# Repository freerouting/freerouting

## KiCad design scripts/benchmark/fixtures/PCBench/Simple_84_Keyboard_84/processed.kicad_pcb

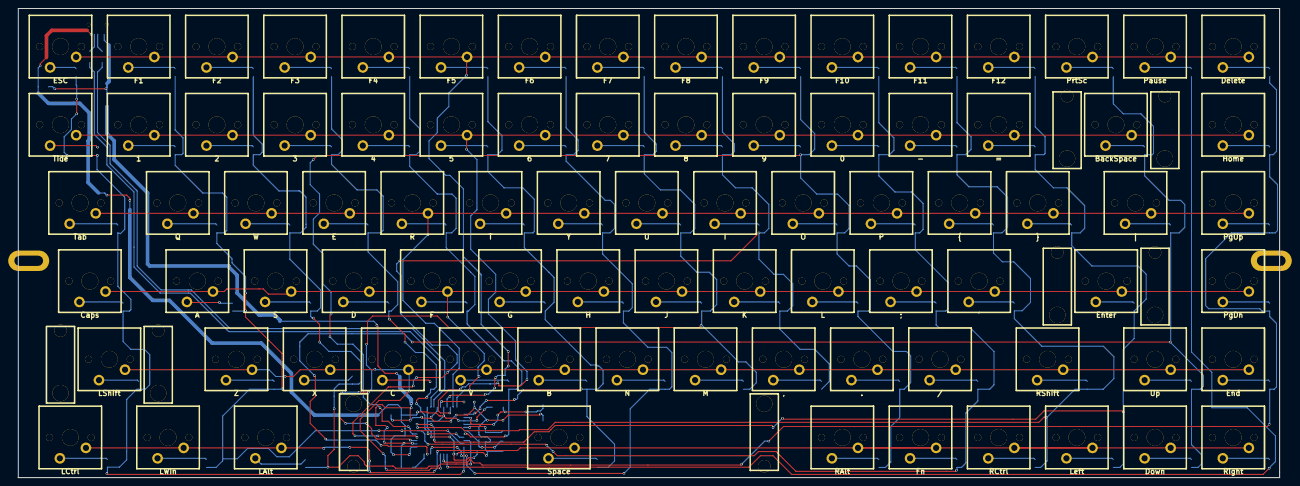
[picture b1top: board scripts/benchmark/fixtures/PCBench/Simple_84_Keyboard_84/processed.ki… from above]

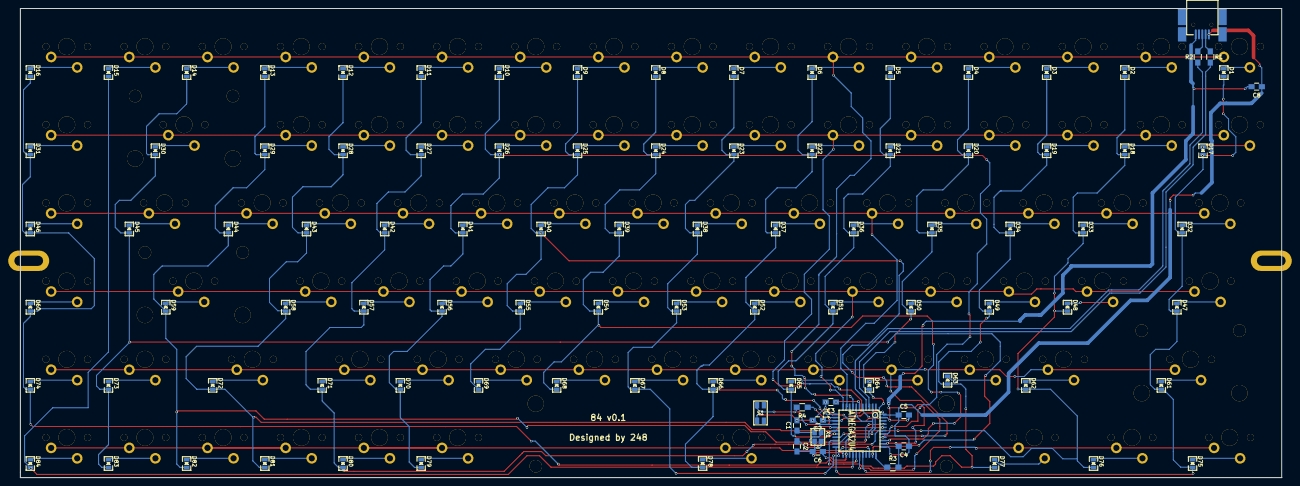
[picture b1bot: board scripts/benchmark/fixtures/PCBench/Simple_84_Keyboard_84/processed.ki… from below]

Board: 2 copper layers, 307.3 x 114.3 mm, 194 parts (100 on the bottom side), 117 nets.

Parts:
C1, C2: 22pF; C_0805_HandSoldering
C3, C8: 1uF; C_0805_HandSoldering
C4, C5, C6, C7: 100nF; C_0805_HandSoldering
D1, D2, D3, D4, D5, D6, D7, D8, D9, D10, D11, D12, D13, D14, D15, D16, D17, D18, D19, D20, D21, D22, D23, D24, D25, D26, D27, D28, D29, D30, D31, D32, D33, D34, D35, D36, D37, D38, D39, D40, D41, D42, D43, D44, D45, D46, D47, D48, D49, D50, D51, D52, D53, D54, D55, D56, D57, D58, D59, D60, D61, D62, D63, D64, D65, D66, D67, D68, D69, D70, D71, D72, D73, D74, D75, D76, D77, D78, D79, D80, D81, D82, D83, D84: DIODE; SM0805D
IC1: ATMEGA32U4; TQFP44
J1: USBMINI_B05; 67503
MXLED: VAL**; PKRHSL
MXLED_2: VAL**; PKRHSL
MXST: VAL**; MXST
MXST_2, MXST_3, MXST_4, MXST_5, MXST_6, MXST_7, MXST_8: VAL**; MXST
R1, R2: 22R; R_0805_HandSoldering
R3, R4: 10K; R_0805_HandSoldering
S1: DTSM-6; TACT_4x3
S2: ESC; MX1A-simple
S3: F1; MX1A-simple
S4: F2; MX1A-simple
S5: F3; MX1A-simple
S6: F4; MX1A-simple
S7: F5; MX1A-simple
S8: F6; MX1A-simple
S9: F7; MX1A-simple
S10: F8; MX1A-simple
S11: F9; MX1A-simple
S12: F10; MX1A-simple
S13: F11; MX1A-simple
S14: F12; MX1A-simple
S15: PrtSc; MX1A-simple
S16: Pause; MX1A-simple
S17: Delete; MX1A-simple
S18: Tide; MX1A-simple
S19: 1; MX1A-simple
S20: 2; MX1A-simple
S21: 3; MX1A-simple
S22: 4; MX1A-simple
S23: 5; MX1A-simple
S24: 6; MX1A-simple
S25: 7; MX1A-simple
S26: 8; MX1A-simple
S27: 9; MX1A-simple
S28: 0; MX1A-simple
S29: -; MX1A-simple
S30: =; MX1A-simple
S31: BackSpace; MX1A-simple
S32: Home; MX1A-simple
S33: Tab; MX1A-simple
S34: Q; MX1A-simple
S35: W; MX1A-simple
S36: E; MX1A-simple
S37: R; MX1A-simple
S38: T; MX1A-simple
S39: Y; MX1A-simple
S40: U; MX1A-simple
S41: I; MX1A-simple
S42: O; MX1A-simple
S43: P; MX1A-simple
S44: {; MX1A-simple
S45: }; MX1A-simple
S46: |; MX1A-simple
S47: PgUp; MX1A-simple
S48: Caps; MX1A-simple
S49: A; MX1A-simple
S50: S; MX1A-simple
S51: D; MX1A-simple
S52: F; MX1A-simple
S53: G; MX1A-simple
S54: H; MX1A-simple
S55: J; MX1A-simple
S56: K; MX1A-simple
S57: L; MX1A-simple
S58: ;; MX1A-simple
S59: '; MX1A-simple
S60: Enter; MX1A-simple
S61: PgDn; MX1A-simple
S62: LShift; MX1A-simple
S63: Z; MX1A-simple
S64: X; MX1A-simple
S65: C; MX1A-simple
S66: V; MX1A-simple
S67: B; MX1A-simple
S68: N; MX1A-simple
S69: M; MX1A-simple
S70: ,; MX1A-simple
S71: .; MX1A-simple
S72: /; MX1A-simple
S73: RShift; MX1A-simple
S74: Up; MX1A-simple
S75: End; MX1A-simple
S76: LCtrl; MX1A-simple
S77: LWin; MX1A-simple
S78: LAlt; MX1A-simple
S79: Space; MX1A-simple
S80: RAlt; MX1A-simple
S81: Fn; MX1A-simple
S82: RCtrl; MX1A-simple
S83: Left; MX1A-simple
S84: Down; MX1A-simple
S85: Right; MX1A-simple
X1: ASX4; ASX3F

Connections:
/switch_matrix/Col1: D1.1, D17.1, D32.1, D47.1, D61.1, D75.1, IC1.22
/switch_matrix/Col2: D2.1, D18.1, D33.1, D48.1, D62.1, D76.1, IC1.21
/switch_matrix/Col3: D3.1, D19.1, D34.1, D49.1, D63.1, D77.1, IC1.20
/switch_matrix/Col4: D4.1, D20.1, D35.1, D50.1, D64.1, IC1.19
/switch_matrix/Col5: D5.1, D21.1, D36.1, D51.1, D65.1, IC1.18
/switch_matrix/Col6: D6.1, D22.1, D37.1, D52.1, D66.1, D78.1, IC1.12
/switch_matrix/Col7: D7.1, D23.1, D38.1, D53.1, D67.1, IC1.31
/switch_matrix/Col8: D8.1, D24.1, D39.1, D54.1, D68.1, IC1.36
/switch_matrix/Col9: D9.1, D25.1, D40.1, D55.1, D69.1, IC1.37
/switch_matrix/Col10: D10.1, D26.1, D41.1, D56.1, D70.1, D79.1, IC1.38
/switch_matrix/Col11: D11.1, D27.1, D42.1, D57.1, D71.1, D80.1, IC1.39
/switch_matrix/Col12: D12.1, D28.1, D43.1, D58.1, D72.1, D81.1, IC1.40
/switch_matrix/Col13: D13.1, D29.1, D44.1, D59.1, D82.1, IC1.41
/switch_matrix/Col14: D14.1, D30.1, D45.1, D73.1, D83.1, IC1.32
/switch_matrix/Col15: D15.1, D84.1, IC1.26
/switch_matrix/Col16: D16.1, D31.1, D46.1, D60.1, D74.1, IC1.27
/switch_matrix/Row1: IC1.8, S2.1, S3.1, S4.1, S5.1, S6.1, S7.1, S8.1, S9.1, S10.1, S11.1, S12.1, S13.1, S14.1, S15.1, S16.1, S17.1
/switch_matrix/Row2: IC1.9, S18.1, S19.1, S20.1, S21.1, S22.1, S23.1, S24.1, S25.1, S26.1, S27.1, S28.1, S29.1, S30.1, S31.1, S32.1
/switch_matrix/Row3: IC1.10, S33.1, S34.1, S35.1, S36.1, S37.1, S38.1, S39.1, S40.1, S41.1, S42.1, S43.1, S44.1, S45.1, S46.1, S47.1
/switch_matrix/Row4: IC1.11, S48.1, S49.1, S50.1, S51.1, S52.1, S53.1, S54.1, S55.1, S56.1, S57.1, S58.1, S59.1, S60.1, S61.1
/switch_matrix/Row5: IC1.28, S62.1, S63.1, S64.1, S65.1, S66.1, S67.1, S68.1, S69.1, S70.1, S71.1, S72.1, S73.1, S74.1, S75.1
/switch_matrix/Row6: IC1.29, S76.1, S77.1, S78.1, S79.1, S80.1, S81.1, S82.1, S83.1, S84.1, S85.1
GND: C1.2, C2.2, C3.2, C4.2, C5.2, C6.2, C7.2, C8.2, IC1.5, IC1.15, IC1.23, IC1.35, IC1.43, J1.5, R3.2, S1.1, X1.2, X1.4
unnamed: C1.1, IC1.16, X1.1
unnamed: C2.1, IC1.17, X1.3
unnamed: C3.1, IC1.6
unnamed: D1.2, S2.2
unnamed: D2.2, S3.2
unnamed: D3.2, S4.2
unnamed: D4.2, S5.2
unnamed: D5.2, S6.2
unnamed: D6.2, S7.2
unnamed: D7.2, S8.2
unnamed: D8.2, S9.2
unnamed: D9.2, S10.2
unnamed: D10.2, S11.2
unnamed: D11.2, S12.2
unnamed: D12.2, S13.2
unnamed: D13.2, S14.2
unnamed: D14.2, S15.2
unnamed: D15.2, S16.2
unnamed: D16.2, S17.2
unnamed: D17.2, S18.2
unnamed: D18.2, S19.2
unnamed: D19.2, S20.2
unnamed: D20.2, S21.2
unnamed: D21.2, S22.2
unnamed: D22.2, S23.2
unnamed: D23.2, S24.2
unnamed: D24.2, S25.2
unnamed: D25.2, S26.2
unnamed: D26.2, S27.2
unnamed: D27.2, S28.2
unnamed: D28.2, S29.2
unnamed: D29.2, S30.2
unnamed: D30.2, S31.2
unnamed: D31.2, S32.2
unnamed: D32.2, S33.2
unnamed: D33.2, S34.2
unnamed: D34.2, S35.2
unnamed: D35.2, S36.2
unnamed: D36.2, S37.2
unnamed: D37.2, S38.2
unnamed: D38.2, S39.2
unnamed: D39.2, S40.2
unnamed: D40.2, S41.2
unnamed: D41.2, S42.2
unnamed: D42.2, S43.2
unnamed: D43.2, S44.2
unnamed: D44.2, S45.2
unnamed: D45.2, S46.2
unnamed: D46.2, S47.2
unnamed: D47.2, S48.2
unnamed: D48.2, S49.2
unnamed: D49.2, S50.2
unnamed: D50.2, S51.2
unnamed: D51.2, S52.2
unnamed: D52.2, S53.2
unnamed: D53.2, S54.2
unnamed: D54.2, S55.2
unnamed: D55.2, S56.2
unnamed: D56.2, S57.2
unnamed: D57.2, S58.2
unnamed: D58.2, S59.2
unnamed: D59.2, S60.2
unnamed: D60.2, S61.2
unnamed: D61.2, S62.2
unnamed: D62.2, S63.2
unnamed: D63.2, S64.2
unnamed: D64.2, S65.2
unnamed: D65.2, S66.2
unnamed: D66.2, S67.2
unnamed: D67.2, S68.2
unnamed: D68.2, S69.2
unnamed: D69.2, S70.2
unnamed: D70.2, S71.2
unnamed: D71.2, S72.2
unnamed: D72.2, S73.2
unnamed: D73.2, S74.2
unnamed: D74.2, S75.2
unnamed: D75.2, S76.2
unnamed: D76.2, S77.2
unnamed: D77.2, S78.2
unnamed: D78.2, S79.2
unnamed: D79.2, S80.2
unnamed: D80.2, S81.2
unnamed: D81.2, S82.2
unnamed: D82.2, S83.2
unnamed: D83.2, S84.2
unnamed: D84.2, S85.2
unnamed: IC1.3, R1.2
unnamed: IC1.4, R2.1
unnamed: IC1.13, R4.2, S1.3
unnamed: IC1.33, R3.1
unnamed: J1.2, R1.1
unnamed: J1.3, R2.2
VCC: C4.1, C5.1, C6.1, C7.1, C8.1, IC1.2, IC1.7, IC1.14, IC1.24, IC1.34, IC1.44, J1.1, R4.1

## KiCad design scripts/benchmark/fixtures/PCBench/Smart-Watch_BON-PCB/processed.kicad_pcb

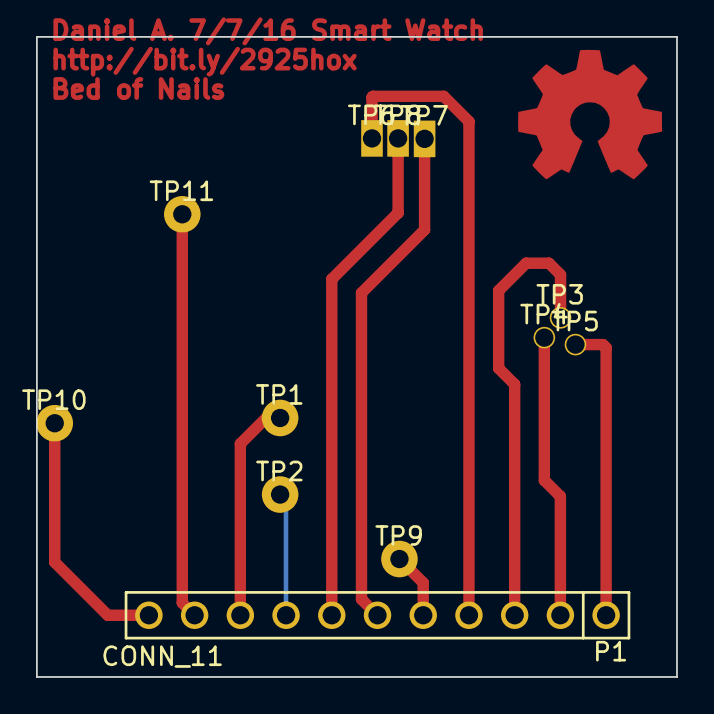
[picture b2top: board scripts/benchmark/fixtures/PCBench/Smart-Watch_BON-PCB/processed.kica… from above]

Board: 2 copper layers, 35.6 x 35.6 mm, 12 parts (0 on the bottom side), 11 nets.

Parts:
P1: CONN_11; PIN-ARRAY_11x1
TP1: 3.3VDC; 1_Pin_0.04dia
TP2: GND; 1_Pin_0.04dia
TP3: PGD; TP2_SW
TP4: PGC; TP2_SW
TP5: MCLR; TP2_SW
TP6: RTCC; TP_SW
TP7: SCL; TP_SW
TP8: SDA; TP_SW
TP9: +13VDC; 1_Pin_0.04dia
TP10: USB +5VDC; 1_Pin_0.04dia
TP11: VBAT; 1_Pin_0.04dia

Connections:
/+3.3VDC: P1.9, TP1.1
/+13VDC: P1.5, TP9.1
/GND: P1.8, TP2.1
/MCLR: P1.1, TP5.1
/PGC: P1.2, TP4.1
/PGD: P1.3, TP3.1
/RTCC: P1.4, TP6.1
/SCL: P1.6, TP7.1
/SDA: P1.7, TP8.1
/USB +5VDC: P1.11, TP10.1
/VBAT: P1.10, TP11.1

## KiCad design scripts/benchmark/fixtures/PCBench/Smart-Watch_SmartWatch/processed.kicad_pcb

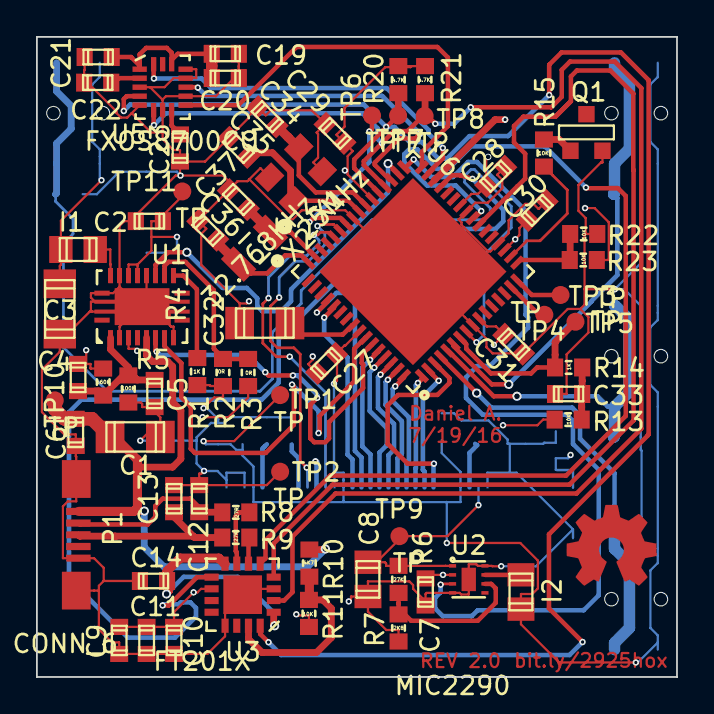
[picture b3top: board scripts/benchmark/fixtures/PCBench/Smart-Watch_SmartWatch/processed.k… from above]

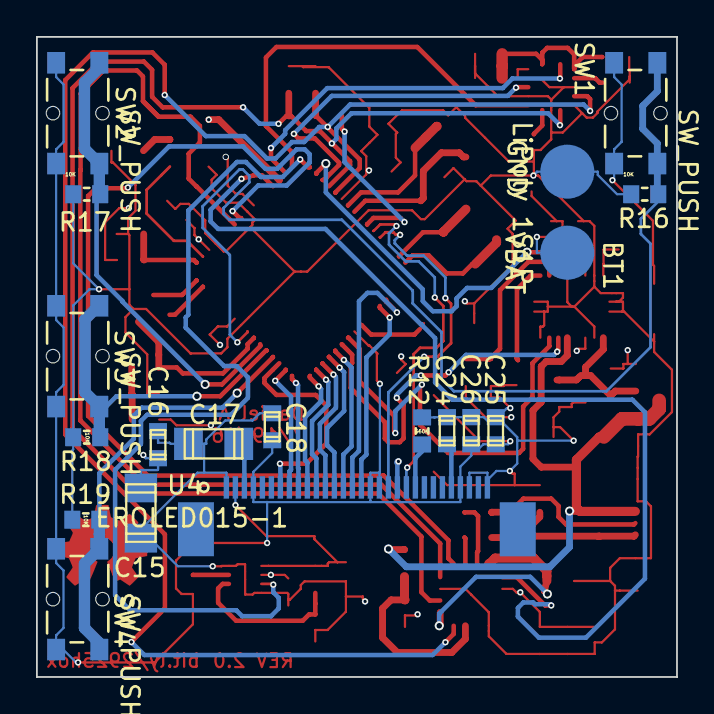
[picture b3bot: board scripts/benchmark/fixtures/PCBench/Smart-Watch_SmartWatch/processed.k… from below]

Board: 4 copper layers, 35.6 x 35.6 mm, 88 parts (18 on the bottom side), 65 nets.

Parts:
BT1: LiPoly 1S1P; CON_SM_3mm_2pin
C1, C3, C15, C32: 10u; c_1206
C2, C9, C19, C25: 4.7u; c_0603
C4: 27p; c_0603
C5: 180p; c_0603
C6, C10, C11, C14, C16, C20, C21, C22, C23, C26, C27, C28, C29, C30, C31, C33: 100n; c_0603
C7, C18, C24: 1u; c_0603
C8: 10u; c_0805
C12, C13: 47p; c_0603
C17: 4.7u; c_1206
C34, C35: 15p; c_0603
C36, C37: 9p1; c_0603
I1, I2: 10uH; r_0805
P1: CONN_6; USB-Micro-B
Q1: MMBT2222A; SOT23EBC
R1, R14: 1K; r_0603
R2, R3: 0R; r_0603
R4, R12: 560K; r_0603
R5: 100K; r_0603
R6: 27K; r_0603
R7: 2K8; r_0603
R8, R9: 27R; r_0603
R10: 4K7; r_0603
R11, R13, R15, R16, R17, R18, R19, R22, R23: 10K; r_0603
R20, R21: 4.7K; r_0603
SW1, SW2, SW3, SW4: SW_PUSH; 4.7x3.5mm_TCK_SW
TP1, TP2, TP3, TP4, TP5, TP6, TP7, TP8, TP9, TP10, TP11: TP; TP-1mm
U1: BQ25010; 20-VFQFN
U2: MIC2290; 8-VFDFN
U3: FT201X; QFN-16-ExPad
U4: EROLED015-1; ZIF_30pin_0.5pitch
U5: FXOS8700CQ; QFN-16
U6: PIC32MX370F512H; QFN-64
X1: 25MHz; ABM8
X2: 32.768KHz; Crystal_9HT10

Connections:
+3.3V: C3.1, C4.1, C7.1, C9.1, C10.1, C11.1, C18.1, C25.1, C26.1, C27.1, C28.1, C29.1, C30.1, C31.1, I1.2, I2.1, R4.2, R13.2, R20.1, R21.1, SW1.2, SW2.2, SW3.2, SW4.2, TP1.1, U2.2, U3.10, U4.4, U4.17, U4.18, U4.27, U6.10, U6.19, U6.26, U6.38, U6.57
+13V: C8.1, C15.1, C16.1, R6.1, TP9.1, U2.1, U4.2
/BAT/2: R22.2, R23.1, U6.17
/LCD/Sensors/CS: U4.19, U6.44
/LCD/Sensors/D0: U4.14, U6.60
/LCD/Sensors/D1: U4.13, U6.61
/LCD/Sensors/D2: U4.12, U6.62
/LCD/Sensors/D3: U4.11, U6.63
/LCD/Sensors/D4: U4.10, U6.64
/LCD/Sensors/D5: U4.9, U6.1
/LCD/Sensors/D6: U4.8, U6.2
/LCD/Sensors/D7: U4.7, U6.3
/LCD/Sensors/D/C: U4.20, U6.30
/LCD/Sensors/E: U4.15, U6.52
/LCD/Sensors/FX_RST: U5.16, U6.31
/LCD/Sensors/INT1: U5.11, U6.35
/LCD/Sensors/INT2: U5.9, U6.32
/LCD/Sensors/R/W: U4.16, U6.53
/LCD/Sensors/RES: U4.21, U6.43
/LCD/Sensors/SCL: R20.2, TP7.1, U3.16, U5.4, U6.37
/LCD/Sensors/SDA: R21.2, TP8.1, U3.2, U5.6, U6.36
/MOTOR: R15.2, U6.18
/RTCC: TP6.1, U6.42
/SW1: R16.2, SW1.1, U6.8
/SW2: R17.2, SW2.1, U6.6
/SW3: R18.2, SW3.1, U6.5
/SW4: R19.2, SW4.1, U6.4
/USB/Power/Boost-En: U2.3, U6.33
/USB/Power/CBUS2: U3.5, U6.24
/USB/Power/CBUS4: U3.4, U6.23
/USB/Power/D+: C13.1, P1.3, R9.1
/USB/Power/D-: C12.1, P1.2, R8.1
/USB/Power/FTDI_RST: U3.9, U6.29
/USB/Power/STAT1: U1.7, U6.59
/USB/Power/STAT2: U1.8, U6.58
/USB/Power/USB +5V: C1.1, C6.1, P1.1, R10.2, TP10.1, U1.6
/USB/Power/nPG: U1.14, U6.34
GND: BT1.2, C1.2, C2.2, C3.2, C5.2, C6.2, C7.2, C8.2, C9.2, C10.2, C11.2, C12.2, C13.2, C14.2, C15.2, C16.2, C17.2, C18.2, C19.2, C20.2, C21.2, C22.2, C23.2, C24.2, C25.2, C26.2, C27.2, C28.2, C29.2, C30.2, C31.2, C32.2, C33.2, C34.2, C35.2, C36.2, C37.2, P1.5, P1.6, Q1.1, R1.2, R2.2, R5.1, R7.2, R11.1, R12.1, R16.1, R17.1, R18.1, R19.1, R23.2, TP2.1, U1.3, U1.9, U1.15, U1.18, U1.20, U1.21, U2.4, U2.8, U2.9, U3.3, U3.13, U3.17, U4.1, U4.28, U4.30, U5.3, U5.5, U5.7, U5.10, U5.12, U5.13, U6.9, U6.20, U6.25, U6.41, U6.65, X1.3, X1.4
unnamed: C34.1, U6.39, X1.2
unnamed: C35.1, U6.40, X1.1
unnamed: TP3.1, U6.16
unnamed: TP4.1, U6.15
unnamed: C33.1, R13.1, R14.1
unnamed: C36.1, U6.48, X2.2
unnamed: C37.1, U6.47, X2.1
unnamed: Q1.2, R15.1
unnamed: R14.2, TP5.1, U6.7
unnamed: C32.1, U6.56
unnamed: I1.1, U1.19
unnamed: C4.2, C5.1, R4.1, R5.2, U1.2
unnamed: I2.2, U2.7
unnamed: R2.1, R3.2, U1.13
unnamed: R1.1, U1.12
unnamed: R10.1, R11.2, U3.15
unnamed: C14.1, U3.1, U3.8
unnamed: R9.2, U3.6
unnamed: R6.2, R7.1, U2.6
unnamed: R8.2, U3.7
unnamed: C19.1, C20.1, C21.1, U5.1, U5.14
unnamed: C22.1, U5.2
unnamed: C23.1, U5.8
unnamed: R12.2, U4.22
unnamed: C24.1, U4.26
unnamed: C17.1, U4.3
VBAT: BT1.1, C2.1, R3.1, R22.1, TP11.1, U1.4, U1.16, U1.17
